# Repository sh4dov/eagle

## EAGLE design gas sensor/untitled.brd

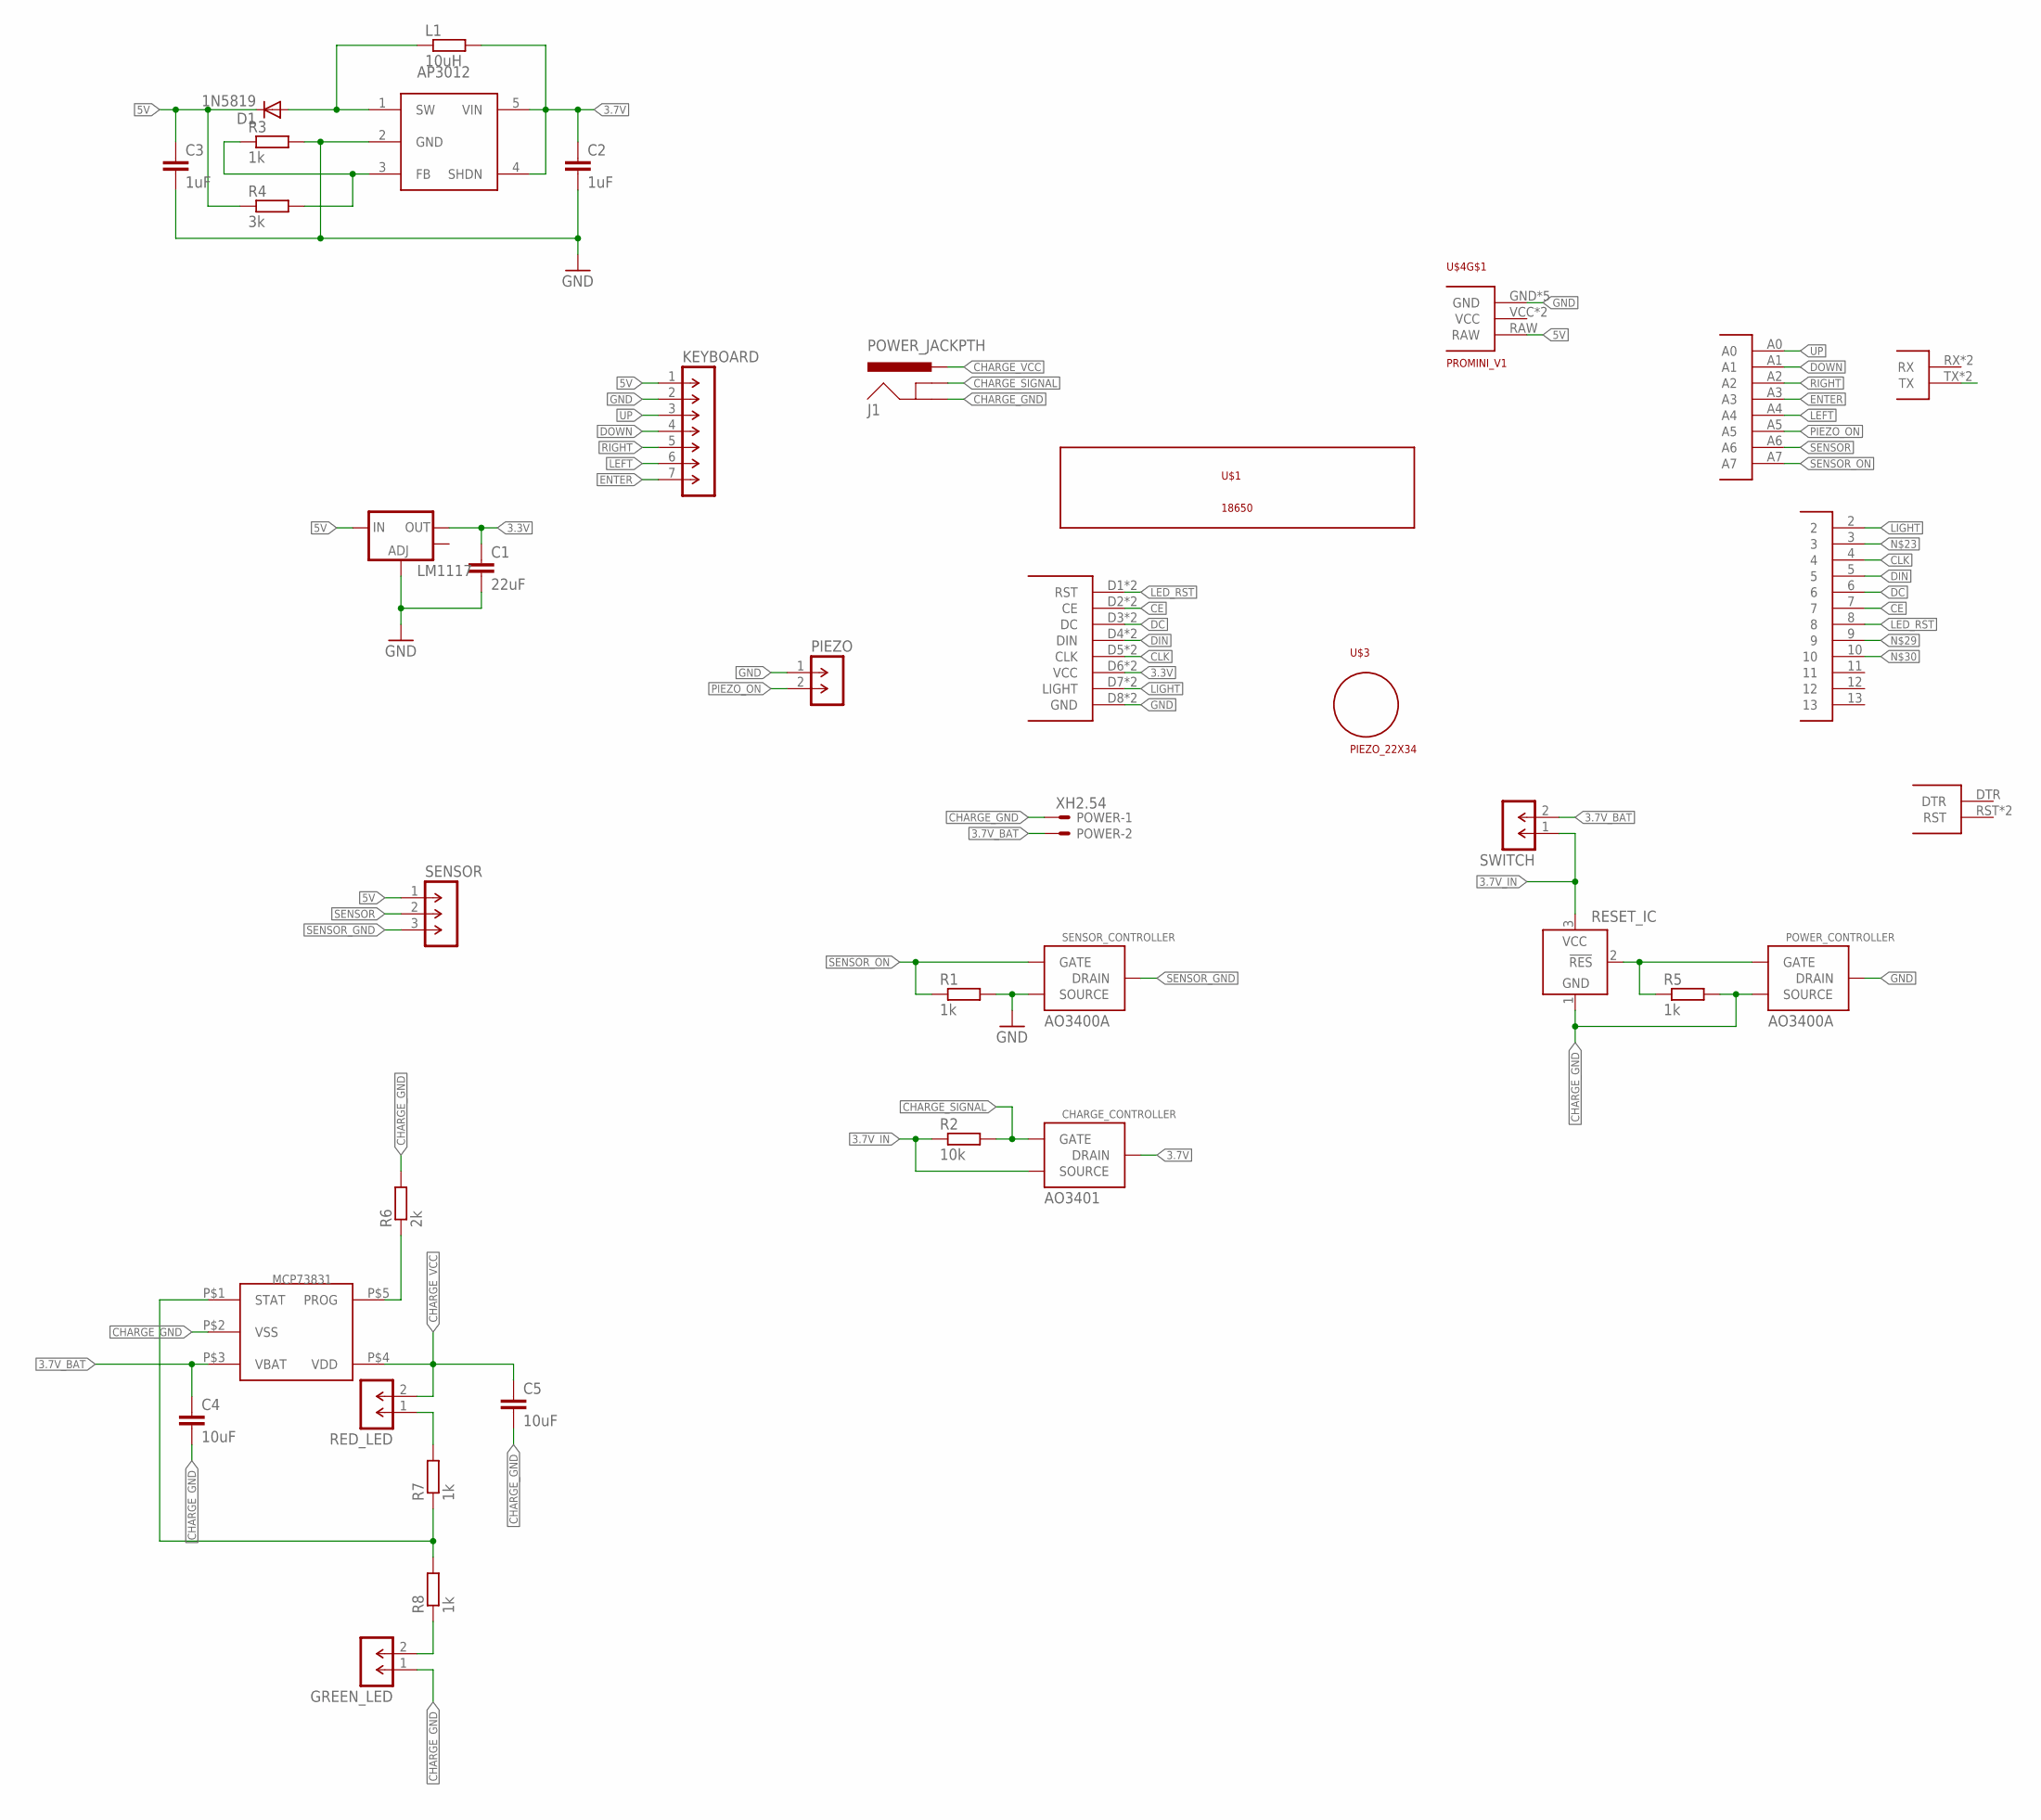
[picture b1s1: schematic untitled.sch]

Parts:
C1: 22uF; C0805K
C2, C3: 1uF; C1206
C4, C5: 10uF; C0805
CHARGE_CONTROLLER: AO3401; SOT-23
D1: 1N5819; DO214AC
GREEN_LED: M-1X02-SIP-100-32Y; SIP-100-02-32Y
J1: POWER_JACKPTH; POWER_JACK_PTH
KEYBOARD: M-1X07-SIP-100-32Y; SIP-100-07-32Y
L1: 10uH; R0805
LM1117: V_REG_LM1117SOT223; SOT223
MCP73831: MCP73831; 5PIN_SOT23
PIEZO: M-1X02-SIP-100-32Y; SIP-100-02-32Y
POWER: XH2.54
POWER_CONTROLLER: AO3400A; SOT-23
R1, R3, R5, R7, R8: 1k; R1206
R2: 10k; R1206
R4: 3k; R1206
R6: 2k; R1206
RED_LED: M-1X02-SIP-100-32Y; SIP-100-02-32Y
RESET_IC: TCM809; SOT23B-3
SENSOR: M-1X03-SIP-100-32Y; SIP-100-03-32Y
SENSOR_CONTROLLER: AO3400A; SOT-23
SWITCH: M-1X02-SIP-100-32Y; SIP-100-02-32Y
U$1: 18650
U$2: NOKIA_5110
U$3: PIEZO_22X34
U$4: PROMINI_V1
U$8: AP3012; SOT-23-5

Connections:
3.3V: C1.1, LM1117.2 (OUT), U$2.D6 (VCC), U$2.U6 (VCC)
3.7V: C2.1, CHARGE_CONTROLLER.3 (DRAIN), L1.2, U$8.4 (SHDN), U$8.5 (VIN)
3.7V_BAT: C4.1, MCP73831.P$3 (VBAT), POWER.2, SWITCH.2
3.7V_IN: CHARGE_CONTROLLER.2 (SOURCE), R2.1, RESET_IC.3 (VCC), SWITCH.1
5V: C3.1, D1.C, KEYBOARD.1, LM1117.3 (IN), R4.1, SENSOR.1, U$4.RAW
CE: U$2.D2 (CE), U$2.U2 (CE), U$4.7
CHARGE_GND: C4.2, C5.2, GREEN_LED.1, J1.GND, MCP73831.P$2 (VSS), POWER.1, POWER_CONTROLLER.2 (SOURCE), R5.2, R6.2, RESET_IC.1 (GND)
CHARGE_SIGNAL: CHARGE_CONTROLLER.1 (GATE), J1.GNDBREAK, R2.2
CHARGE_VCC: C5.1, J1.PWR, MCP73831.P$4 (VDD), RED_LED.2
CLK: U$2.D5 (CLK), U$2.U5 (CLK), U$4.4
DC: U$2.D3 (DC), U$2.U3 (DC), U$4.6
DIN: U$2.D4 (DIN), U$2.U4 (DIN), U$4.5
DOWN: KEYBOARD.4, U$4.A1
ENTER: KEYBOARD.7, U$4.A3
GND: C1.2, C2.2, C3.2, KEYBOARD.2, LM1117.1 (ADJ), PIEZO.1, POWER_CONTROLLER.3 (DRAIN), R1.2, R3.2, SENSOR_CONTROLLER.2 (SOURCE), U$2.D8 (GND), U$2.U8 (GND), U$4.GND, U$4.GND2 (GND), U$4.GND3 (GND), U$4.GND4 (GND), U$4.GND5 (GND), U$8.2 (GND)
LED_RST: U$2.D1 (RST), U$2.U1 (RST), U$4.8
LEFT: KEYBOARD.6, U$4.A4
LIGHT: U$2.D7 (LIGHT), U$2.U7 (LIGHT), U$4.2
unnamed: GREEN_LED.2, R8.1
unnamed: U$4.TX, U$4.TX2 (TX)
unnamed: D1.A, L1.1, U$8.1 (SW)
unnamed: MCP73831.P$5 (PROG), R6.1
unnamed: R3.1, R4.2, U$8.3 (FB)
unnamed: R7.2, RED_LED.1
unnamed: MCP73831.P$1 (STAT), R7.1, R8.2
PIEZO_ON: PIEZO.2, U$4.A5
RIGHT: KEYBOARD.5, U$4.A2
SENSOR: SENSOR.2, U$4.A6
SENSOR_GND: SENSOR.3, SENSOR_CONTROLLER.3 (DRAIN)
SENSOR_ON: R1.1, SENSOR_CONTROLLER.1 (GATE), U$4.A7
SENSOR_ON1: POWER_CONTROLLER.1 (GATE), R5.1, RESET_IC.2 (!RES)
UP: KEYBOARD.3, U$4.A0

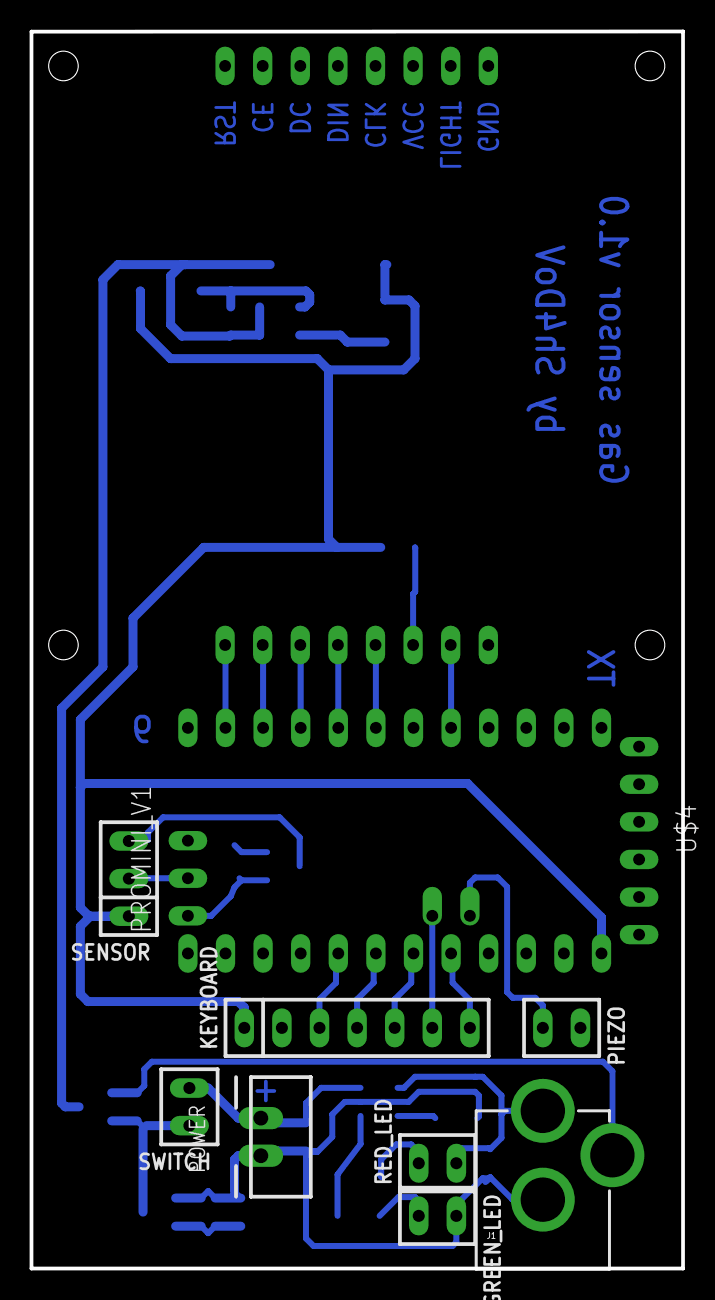
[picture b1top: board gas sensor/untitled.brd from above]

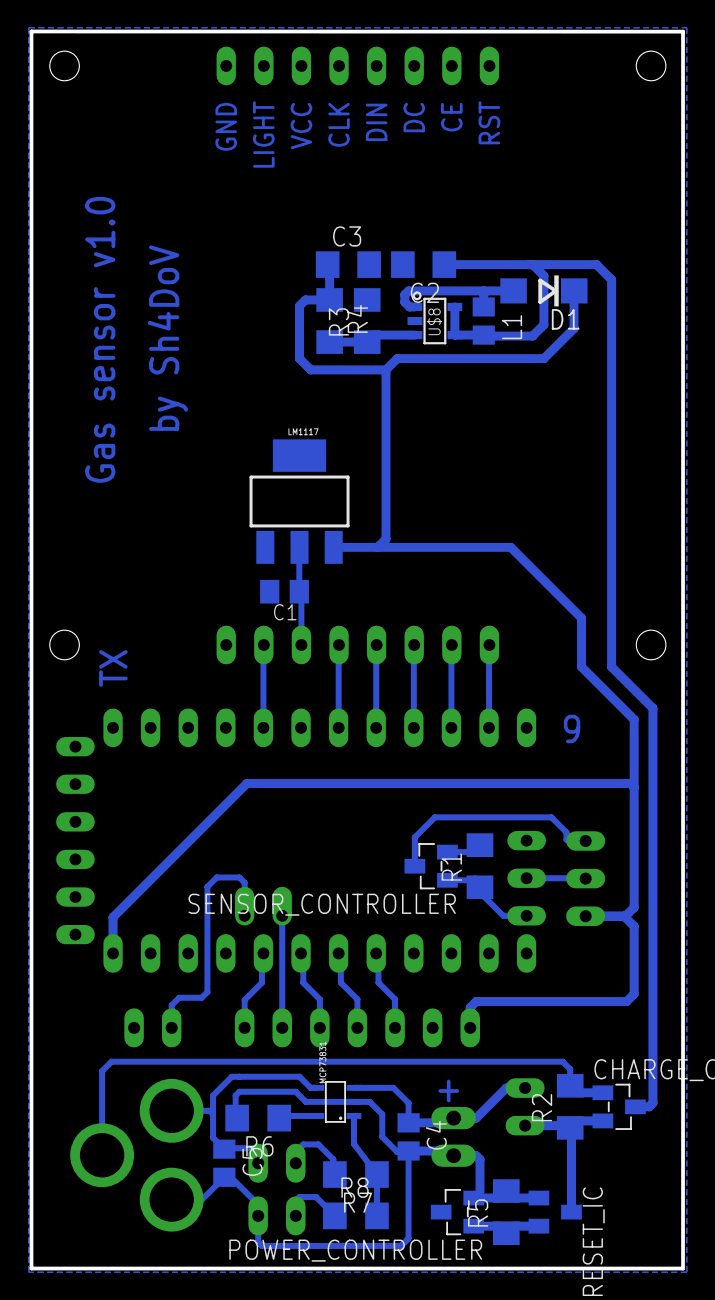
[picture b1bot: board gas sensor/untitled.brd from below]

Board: 2 copper layers, 44.0 x 83.6 mm, 34 parts (22 on the bottom side), 32 nets.

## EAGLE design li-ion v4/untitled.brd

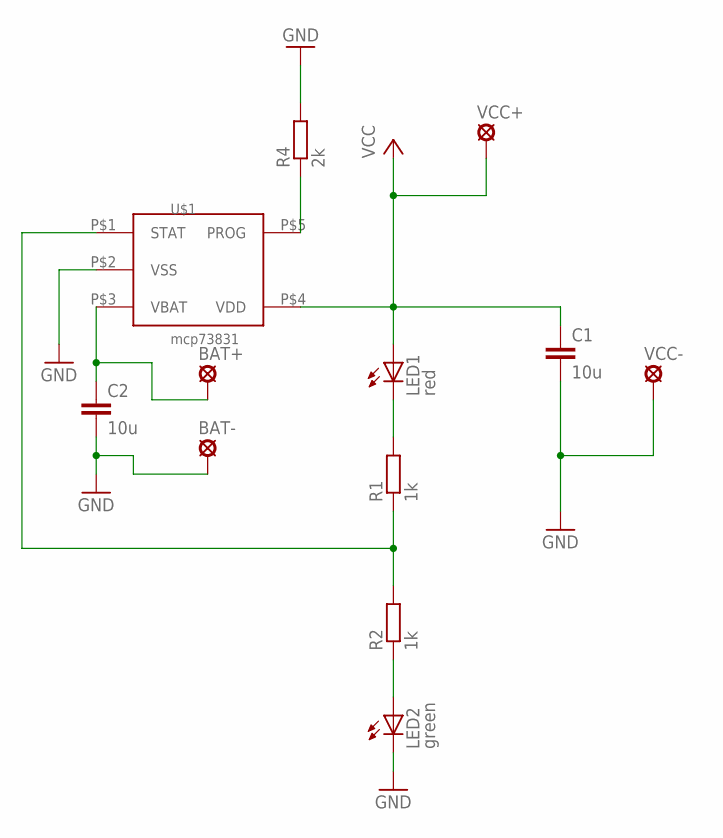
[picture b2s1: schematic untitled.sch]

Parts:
BAT+: LSP10
BAT-: LSP10
C1, C2: 10u; C0805
LED1: red; CHIPLED_0805
LED2: green; CHIPLED_0805
R1, R2: 1k; M1206
R4: 2k; M1206
U$1: mcp73831; 5PIN_SOT23
VCC+: LSP10
VCC-: LSP10

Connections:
GND: BAT-.MP, C1.2, C2.2, LED2.C, R4.2, U$1.P$2 (VSS), VCC-.MP
unnamed: R4.1, U$1.P$5 (PROG)
unnamed: LED1.C, R1.2
unnamed: R1.1, R2.2, U$1.P$1 (STAT)
unnamed: LED2.A, R2.1
unnamed: BAT+.MP, C2.1, U$1.P$3 (VBAT)
VCC: C1.1, LED1.A, U$1.P$4 (VDD), VCC+.MP

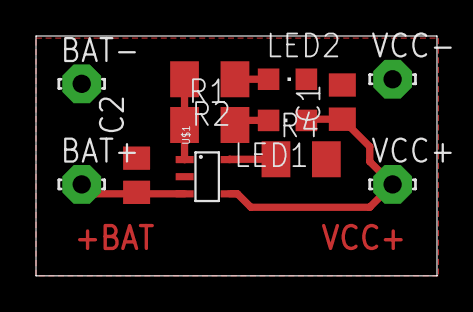
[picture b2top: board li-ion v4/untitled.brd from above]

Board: 2 copper layers, 22.3 x 13.3 mm, 12 parts (0 on the bottom side), 7 nets.

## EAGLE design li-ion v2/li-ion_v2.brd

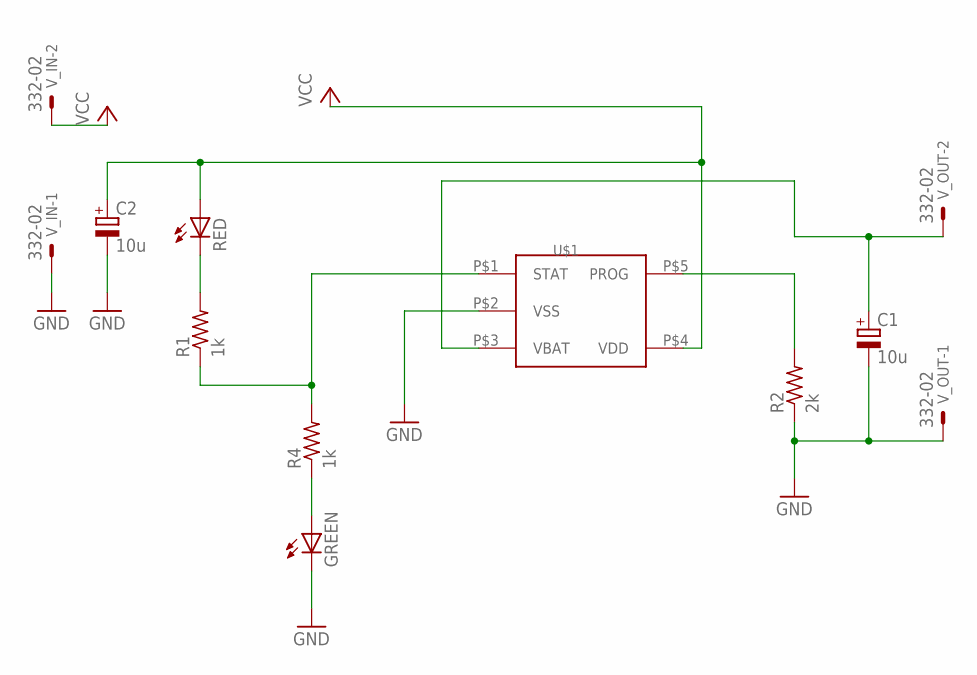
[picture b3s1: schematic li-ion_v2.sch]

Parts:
C1, C2: 10u; E1,8-4
GREEN: LED3MM
R1, R4: 1k; 0204/5
R2: 2k; 0204/5
RED: LED3MM
U$1: MCP73831; 5PIN_SOT23
V_IN: 332-02
V_OUT: 332-02

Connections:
GND: C1.-, C2.-, GREEN.K (C), R2.1, U$1.P$2 (VSS), V_IN.1, V_OUT.1
unnamed: C1.+, U$1.P$3 (VBAT), V_OUT.2
unnamed: R2.2, U$1.P$5 (PROG)
unnamed: R1.1, R4.2, U$1.P$1 (STAT)
unnamed: R1.2, RED.K (C)
unnamed: GREEN.A, R4.1
VCC: C2.+, RED.A, U$1.P$4 (VDD), V_IN.2

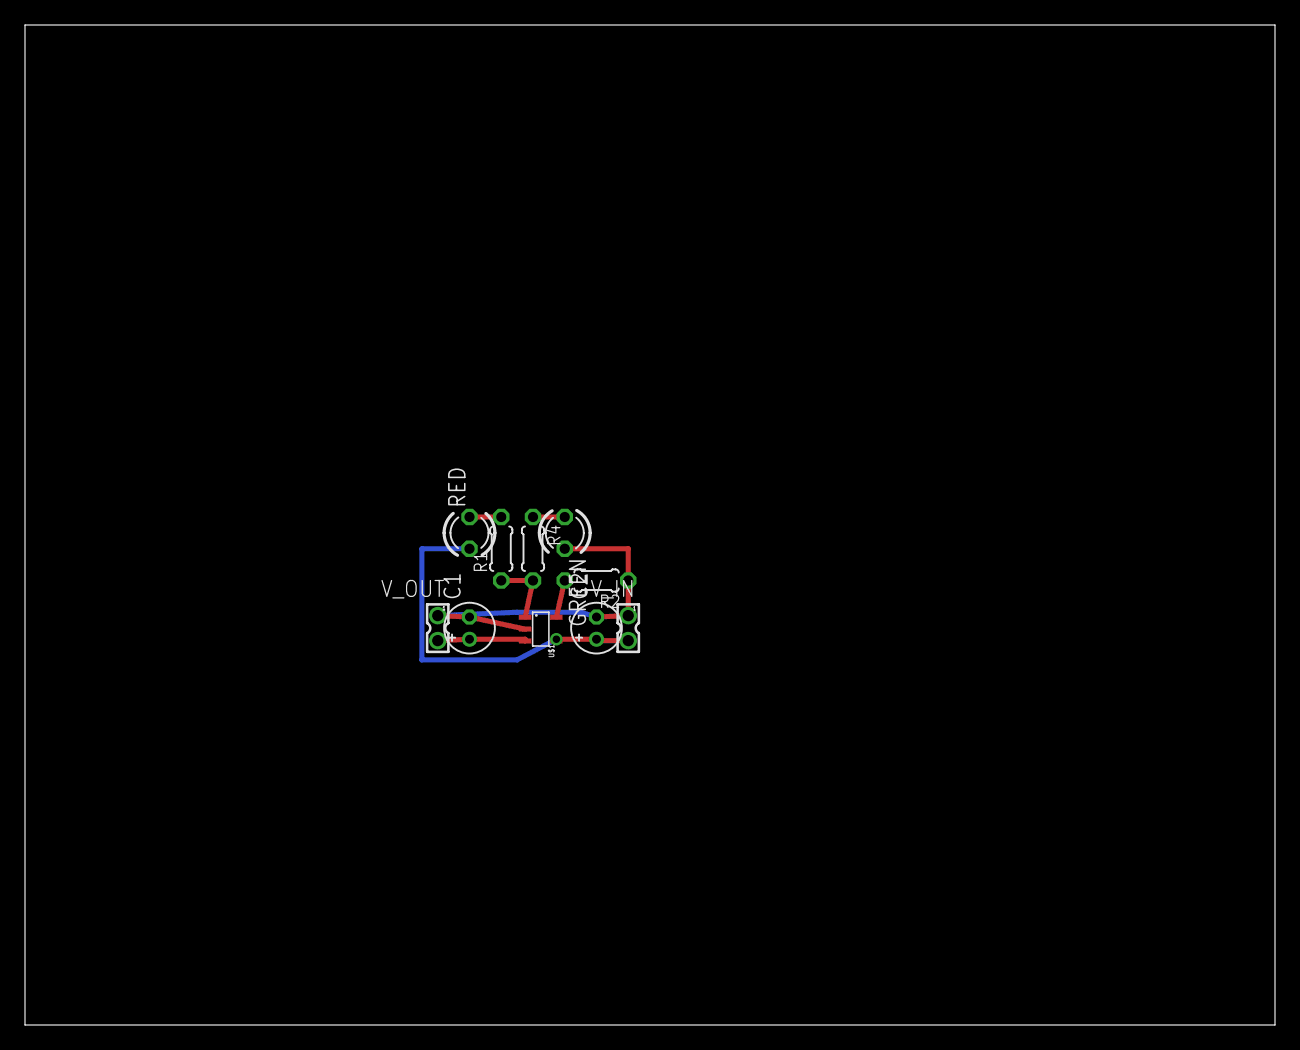
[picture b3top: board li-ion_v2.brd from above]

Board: 2 copper layers, 100.0 x 80.0 mm, 10 parts (0 on the bottom side), 7 nets.

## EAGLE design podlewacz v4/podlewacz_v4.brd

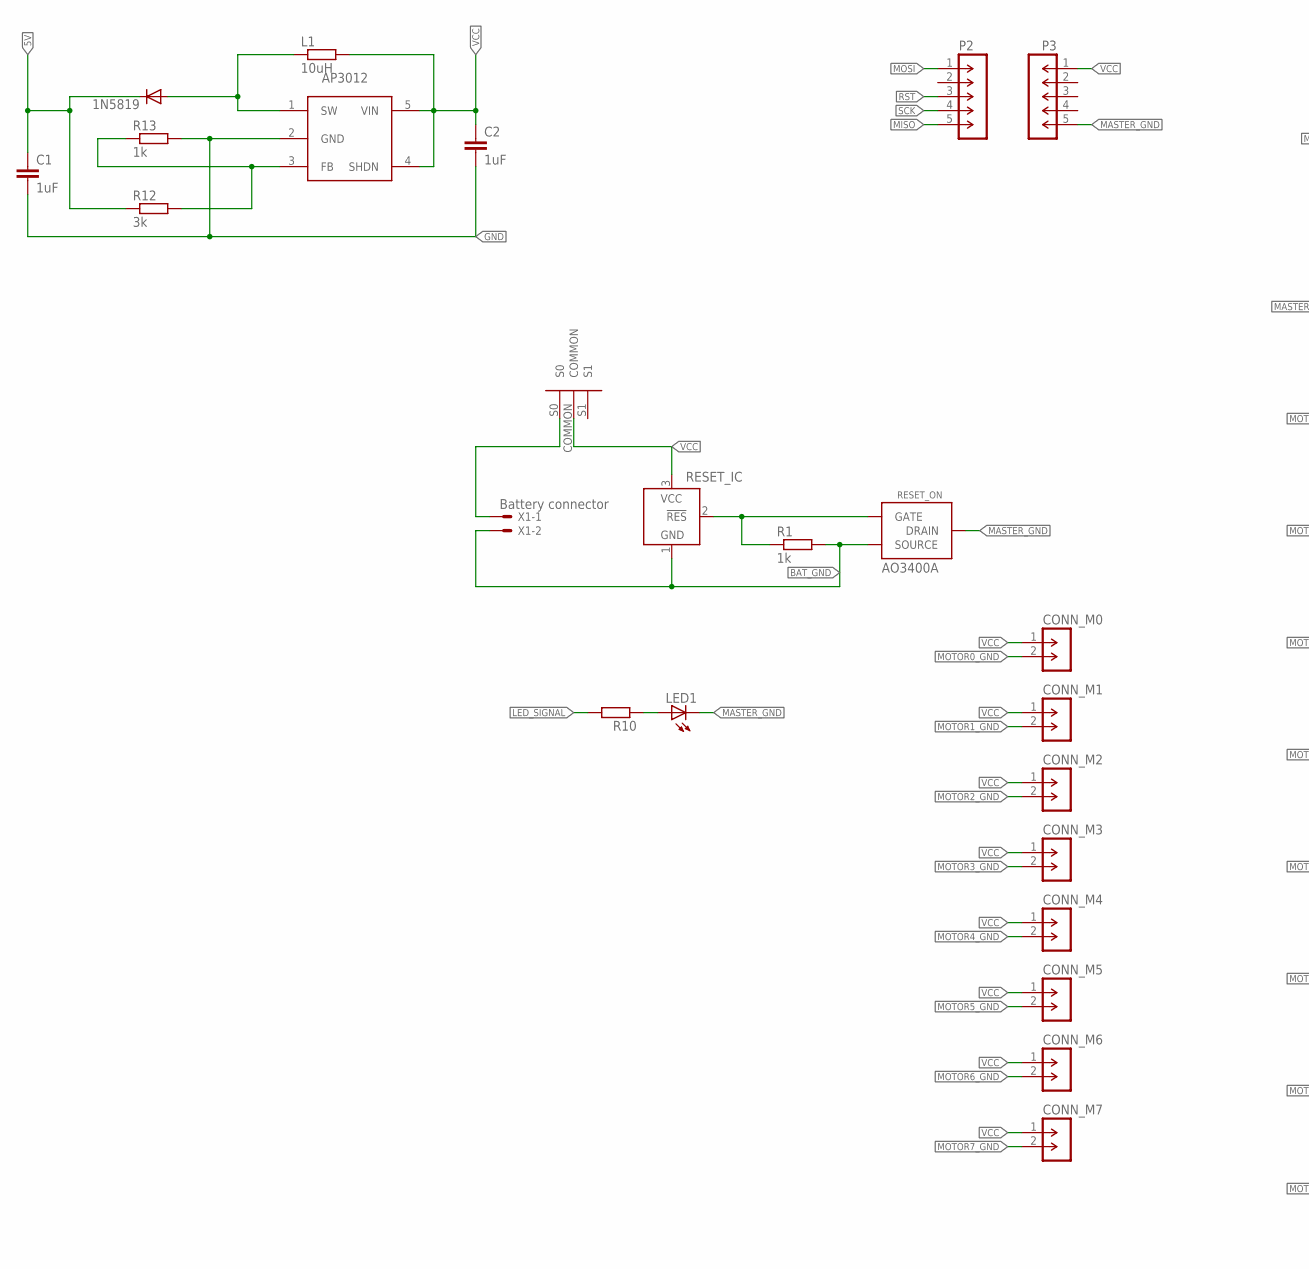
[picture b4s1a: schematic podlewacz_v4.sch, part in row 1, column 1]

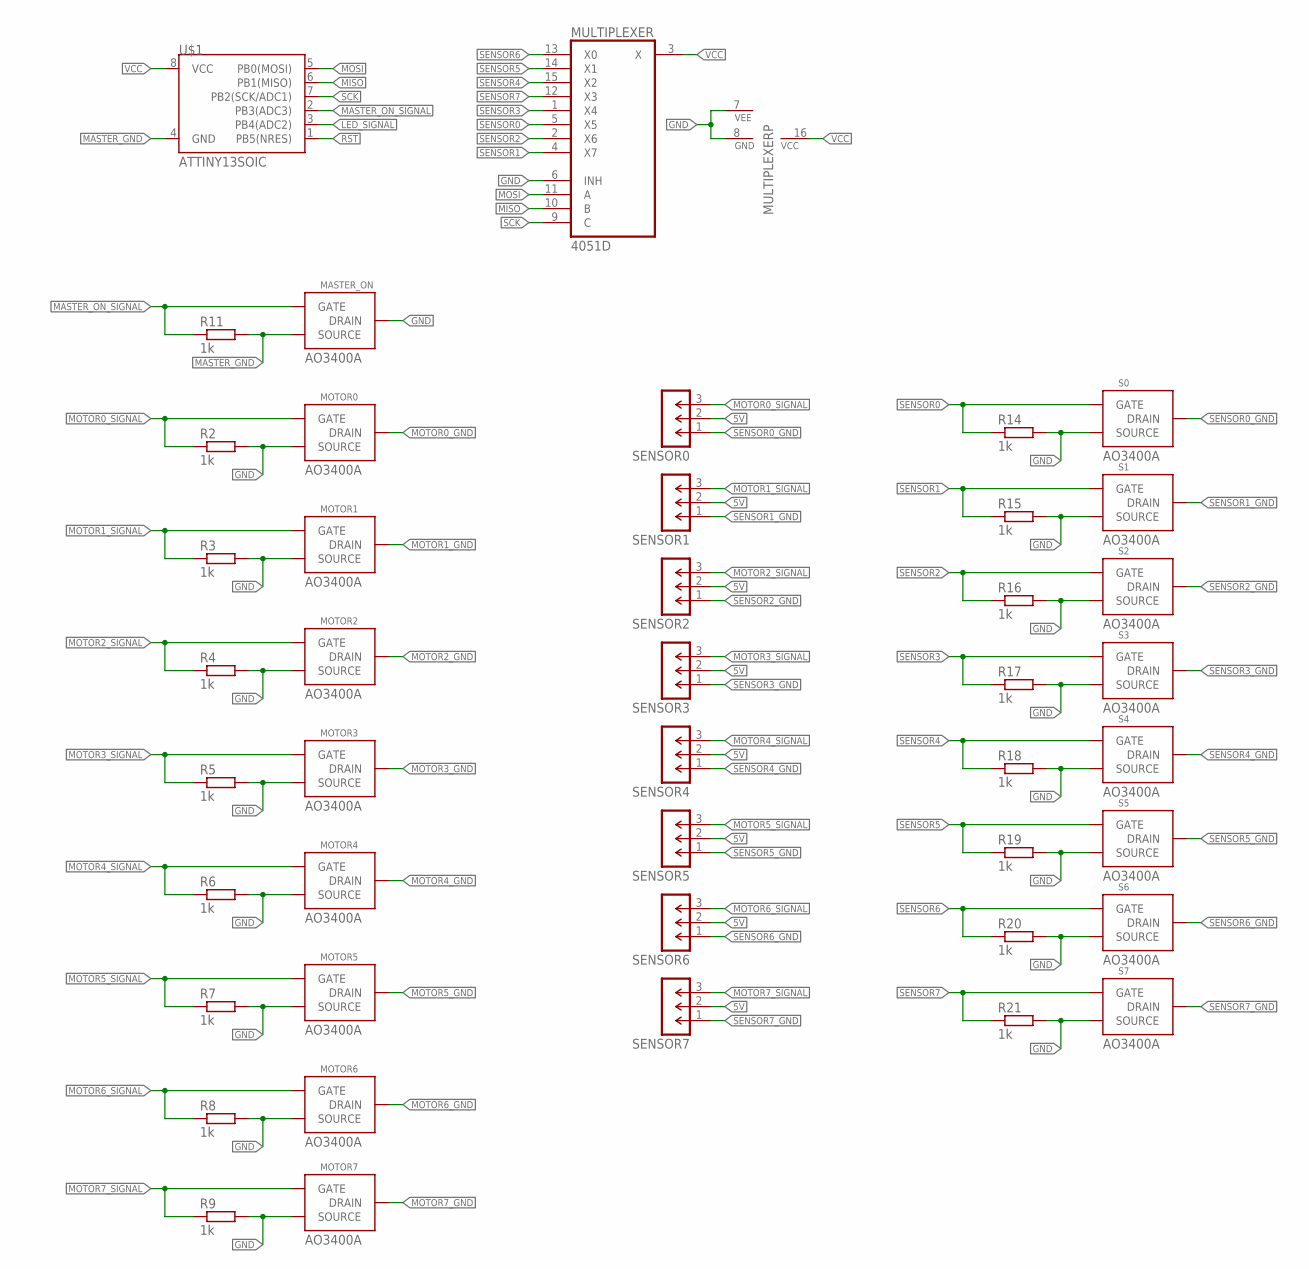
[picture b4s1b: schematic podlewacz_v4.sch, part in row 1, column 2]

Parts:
1N5819: DIODE-DO214AC; DO214AC
AP3012: AP3012; SOT-23-5
C1, C2: 1uF; C1206
CONN_M0, CONN_M1, CONN_M2, CONN_M3, CONN_M4, CONN_M5, CONN_M6, CONN_M7: M-1X02-SIP-100-32Y; SIP-100-02-32Y
L1: 10uH; R0805
LED1: LEDCHIP-LED0805; CHIP-LED0805
MASTER_ON: AO3400A; SOT-23
MOTOR0, MOTOR1, MOTOR2, MOTOR3, MOTOR4, MOTOR5, MOTOR6, MOTOR7: AO3400A; SOT-23
MULTIPLEXER: 4051D; SO16
P2, P3: M-1X05-SIP-100-32; SIP-100-05-32
R1, R2, R3, R4, R5, R6, R7, R8, R9, R11, R13, R14, R15, R16, R17, R18, R19, R20, R21: 1k; M1206
R10: R-EU_M0805; M0805
R12: 3k; M1206
RESET_IC: TCM809; SOT23B-3
RESET_ON: AO3400A; SOT-23
S0, S1, S2, S3, S4, S5, S6, S7: AO3400A; SOT-23
SENSOR0, SENSOR1, SENSOR2, SENSOR3, SENSOR4, SENSOR5, SENSOR6, SENSOR7: M-1X03-SIP-100-32Y; SIP-100-03-32Y
U$1: ATTINY13SOIC; SO08
U$2: SPDT_SLIDE_SWITCH_2_PITCH
X1: Battery connector; 22-23-2021

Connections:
5V: 1N5819.C, C1.1, R12.1, SENSOR0.2, SENSOR1.2, SENSOR2.2, SENSOR3.2, SENSOR4.2, SENSOR5.2, SENSOR6.2, SENSOR7.2
BAT_GND: R1.2, RESET_IC.1 (GND), RESET_ON.2 (SOURCE), X1.2
GND: AP3012.2 (GND), C1.2, C2.2, MASTER_ON.3 (DRAIN), MOTOR0.2 (SOURCE), MOTOR1.2 (SOURCE), MOTOR2.2 (SOURCE), MOTOR3.2 (SOURCE), MOTOR4.2 (SOURCE), MOTOR5.2 (SOURCE), MOTOR6.2 (SOURCE), MOTOR7.2 (SOURCE), MULTIPLEXER.6 (INH), MULTIPLEXER.7 (VEE), MULTIPLEXER.8 (GND), R2.2, R3.2, R4.2, R5.2, R6.2, R7.2, R8.2, R9.2, R13.2, R14.2, R15.2, R16.2, R17.2, R18.2, R19.2, R20.2, R21.2, S0.2 (SOURCE), S1.2 (SOURCE), S2.2 (SOURCE), S3.2 (SOURCE), S4.2 (SOURCE), S5.2 (SOURCE), S6.2 (SOURCE), S7.2 (SOURCE)
LED_SIGNAL: R10.2, U$1.3 (PB4(ADC2))
MASTER_GND: LED1.C, MASTER_ON.2 (SOURCE), P3.5, R11.2, RESET_ON.3 (DRAIN), U$1.4 (GND)
MASTER_ON: R1.1, RESET_IC.2 (!RES), RESET_ON.1 (GATE)
MASTER_ON_SIGNAL: MASTER_ON.1 (GATE), R11.1, U$1.2 (PB3(ADC3))
MISO: MULTIPLEXER.10 (B), P2.5, U$1.6 (PB1(MISO))
MOSI: MULTIPLEXER.11 (A), P2.1, U$1.5 (PB0(MOSI))
MOTOR0_GND: CONN_M0.2, MOTOR0.3 (DRAIN)
MOTOR0_SIGNAL: MOTOR0.1 (GATE), R2.1, SENSOR0.3
MOTOR1_GND: CONN_M1.2, MOTOR1.3 (DRAIN)
MOTOR1_SIGNAL: MOTOR1.1 (GATE), R3.1, SENSOR1.3
MOTOR2_GND: CONN_M2.2, MOTOR2.3 (DRAIN)
MOTOR2_SIGNAL: MOTOR2.1 (GATE), R4.1, SENSOR2.3
MOTOR3_GND: CONN_M3.2, MOTOR3.3 (DRAIN)
MOTOR3_SIGNAL: MOTOR3.1 (GATE), R5.1, SENSOR3.3
MOTOR4_GND: CONN_M4.2, MOTOR4.3 (DRAIN)
MOTOR4_SIGNAL: MOTOR4.1 (GATE), R6.1, SENSOR4.3
MOTOR5_GND: CONN_M5.2, MOTOR5.3 (DRAIN)
MOTOR5_SIGNAL: MOTOR5.1 (GATE), R7.1, SENSOR5.3
MOTOR6_GND: CONN_M6.2, MOTOR6.3 (DRAIN)
MOTOR6_SIGNAL: MOTOR6.1 (GATE), R8.1, SENSOR6.3
MOTOR7_GND: CONN_M7.2, MOTOR7.3 (DRAIN)
MOTOR7_SIGNAL: MOTOR7.1 (GATE), R9.1, SENSOR7.3
unnamed: U$2.S0, X1.1
unnamed: LED1.A, R10.1
unnamed: 1N5819.A, AP3012.1 (SW), L1.1
unnamed: AP3012.3 (FB), R12.2, R13.1
RST: P2.3, U$1.1 (PB5(NRES))
SCK: MULTIPLEXER.9 (C), P2.4, U$1.7 (PB2(SCK/ADC1))
SENSOR0: MULTIPLEXER.5 (X5), R14.1, S0.1 (GATE)
SENSOR0_GND: S0.3 (DRAIN), SENSOR0.1
SENSOR1: MULTIPLEXER.4 (X7), R15.1, S1.1 (GATE)
SENSOR1_GND: S1.3 (DRAIN), SENSOR1.1
SENSOR2: MULTIPLEXER.2 (X6), R16.1, S2.1 (GATE)
SENSOR2_GND: S2.3 (DRAIN), SENSOR2.1
SENSOR3: MULTIPLEXER.1 (X4), R17.1, S3.1 (GATE)
SENSOR3_GND: S3.3 (DRAIN), SENSOR3.1
SENSOR4: MULTIPLEXER.15 (X2), R18.1, S4.1 (GATE)
SENSOR4_GND: S4.3 (DRAIN), SENSOR4.1
SENSOR5: MULTIPLEXER.14 (X1), R19.1, S5.1 (GATE)
SENSOR5_GND: S5.3 (DRAIN), SENSOR5.1
SENSOR6: MULTIPLEXER.13 (X0), R20.1, S6.1 (GATE)
SENSOR6_GND: S6.3 (DRAIN), SENSOR6.1
SENSOR7: MULTIPLEXER.12 (X3), R21.1, S7.1 (GATE)
SENSOR7_GND: S7.3 (DRAIN), SENSOR7.1
VCC: AP3012.4 (SHDN), AP3012.5 (VIN), C2.1, CONN_M0.1, CONN_M1.1, CONN_M2.1, CONN_M3.1, CONN_M4.1, CONN_M5.1, CONN_M6.1, CONN_M7.1, L1.2, MULTIPLEXER.3 (X), MULTIPLEXER.16 (VCC), P3.1, RESET_IC.3 (VCC), U$1.8 (VCC), U$2.COMMON

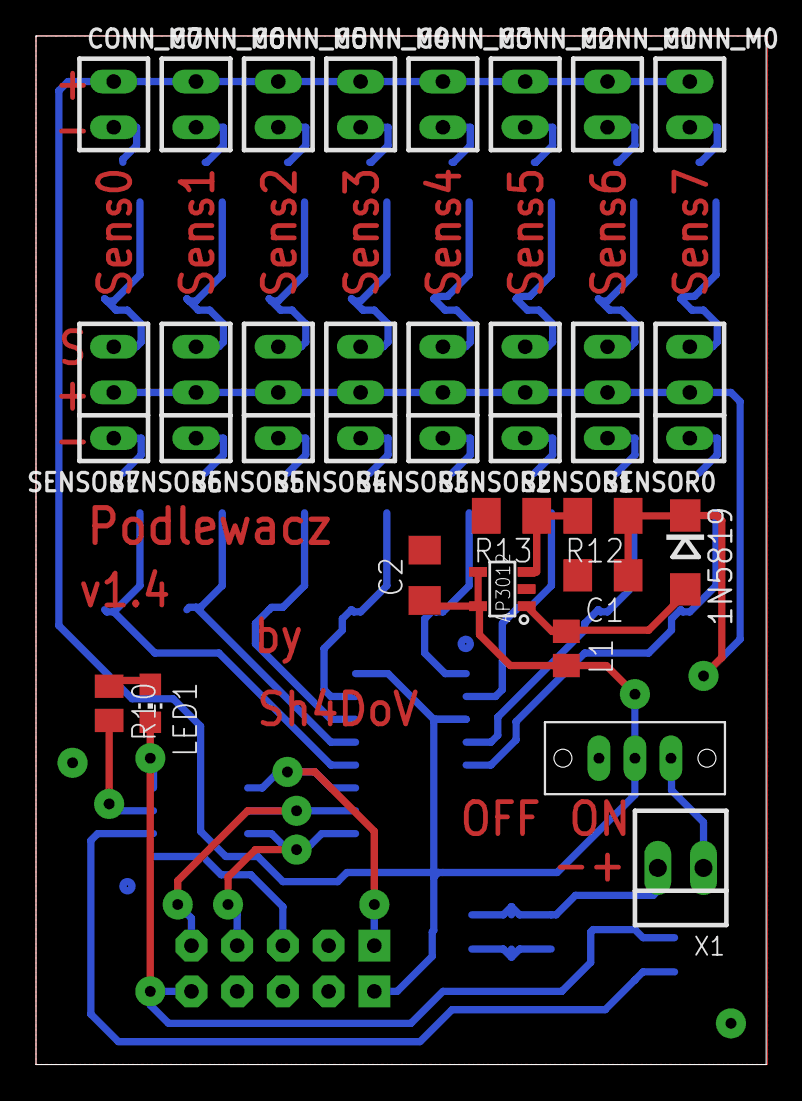
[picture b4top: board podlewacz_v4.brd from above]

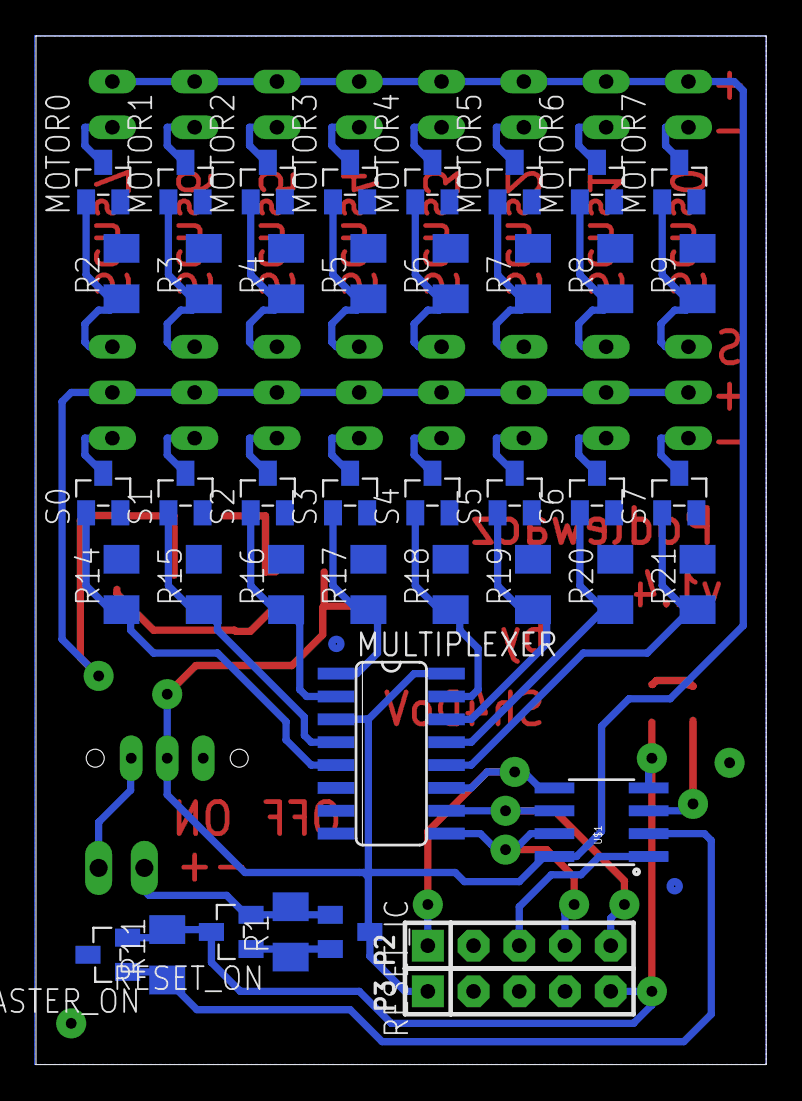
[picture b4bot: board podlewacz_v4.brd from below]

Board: 2 copper layers, 40.6 x 57.1 mm, 68 parts (41 on the bottom side), 48 nets.

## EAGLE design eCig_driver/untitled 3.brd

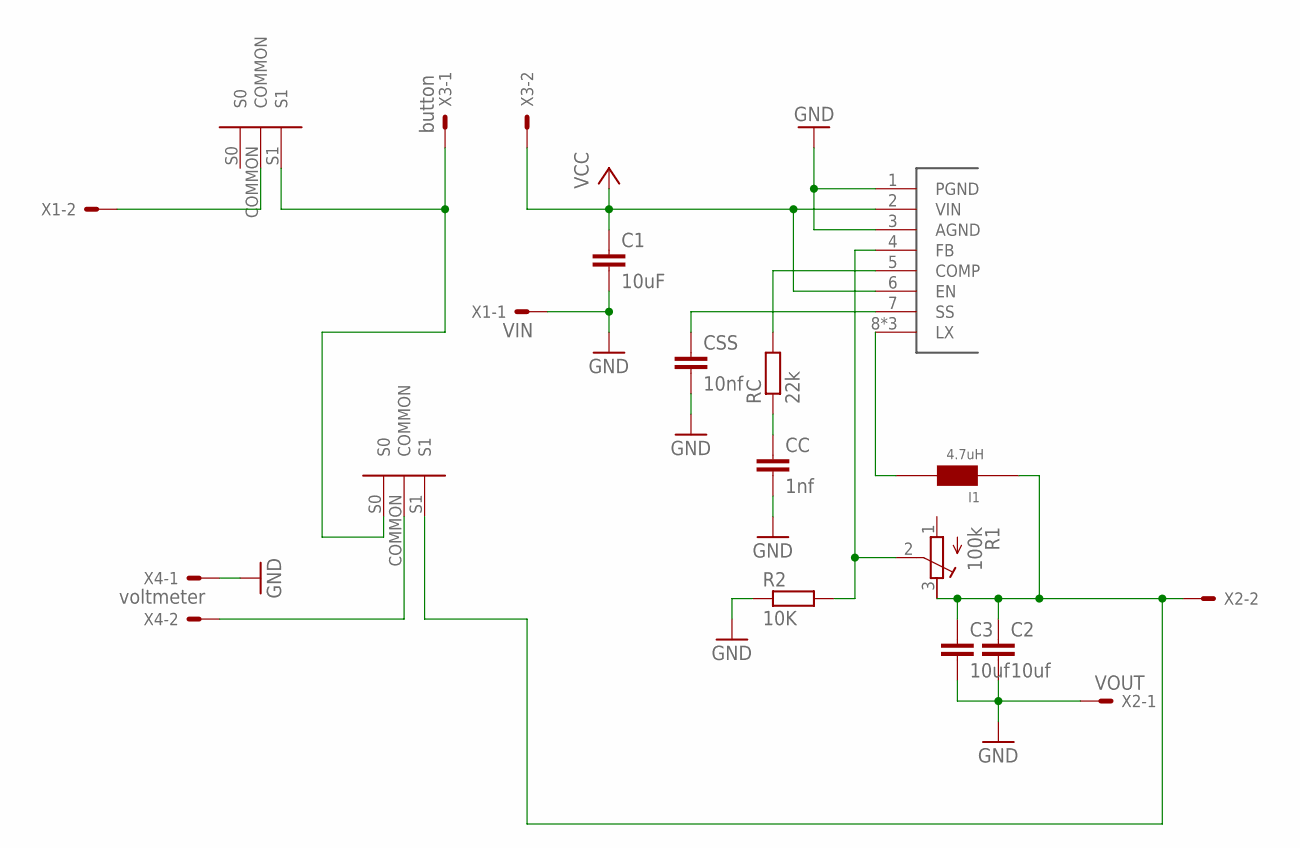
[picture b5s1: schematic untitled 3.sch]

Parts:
C1: 10uF; C0805K
C2, C3: 10uf; C0805K
CC: 1nf; C1206K
CSS: 10nf; C1206K
I1: 4.7uH; RH127
MASTER_ON: SPDT_SLIDE_SWITCH_2_PITCH
METER_SWITCH: SPDT_SLIDE_SWITCH_2_PITCH
R1: 100k; RTRIM64W
R2: 10K; R1206
RC: 22k; R1206
U$3: AOZ1051PI
X1: VIN; XH2.54
X2: VOUT; XH2.54
X3: button; XH2.54
X4: voltmeter; XH2.54

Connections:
GND: C1.2, C2.2, C3.2, CC.2, CSS.2, R2.1, U$3.1 (PGND), U$3.3 (AGND), X1.1, X2.1, X4.1
unnamed: RC.2, U$3.5 (COMP)
unnamed: CC.1, RC.1
unnamed: R1.2 (S), R2.2, U$3.4 (FB)
unnamed: CSS.1, U$3.7 (SS)
unnamed: METER_SWITCH.COMMON, X4.2
unnamed: I1.P$1, U$3.8 (LX), U$3.P$1 (LX), U$3.P$2 (LX)
unnamed: C2.1, C3.1, I1.P$2, METER_SWITCH.S1, R1.3 (E), X2.2
unnamed: MASTER_ON.COMMON, X1.2
unnamed: MASTER_ON.S1, METER_SWITCH.S0, X3.1
VCC: C1.1, U$3.2 (VIN), U$3.6 (EN), X3.2

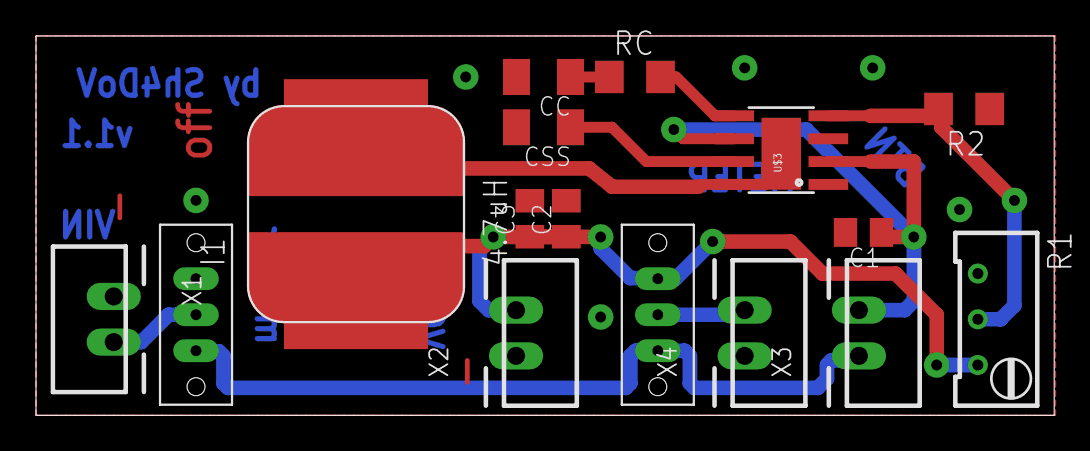
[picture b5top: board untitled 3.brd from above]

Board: 2 copper layers, 56.6 x 21.1 mm, 16 parts (0 on the bottom side), 11 nets.

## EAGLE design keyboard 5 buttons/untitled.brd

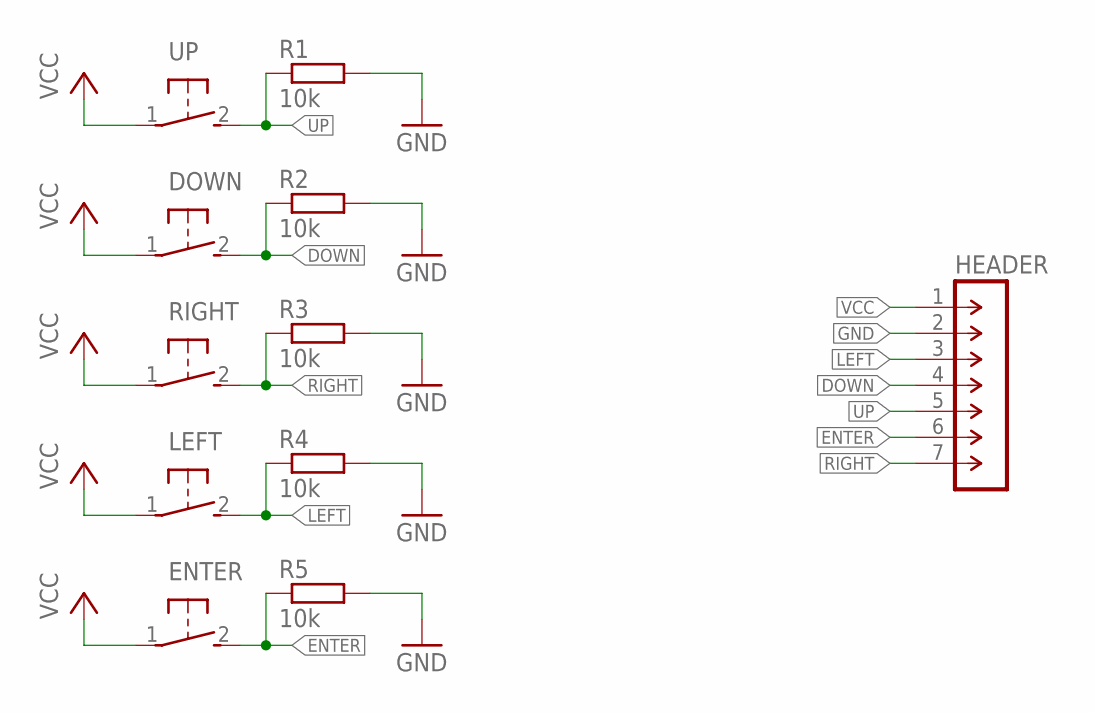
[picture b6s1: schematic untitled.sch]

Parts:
DOWN: DTSM-3
ENTER: DTSM-3
HEADER: M-1X07-SIP-100-32Y; SIP-100-07-32Y
LEFT: DTSM-3
R1, R2, R3, R4, R5: 10k; R1206
RIGHT: DTSM-3
UP: DTSM-3

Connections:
DOWN: DOWN.2, HEADER.4, R2.1
ENTER: ENTER.2, HEADER.6, R5.1
GND: HEADER.2, R1.2, R2.2, R3.2, R4.2, R5.2
LEFT: HEADER.3, LEFT.2, R4.1
RIGHT: HEADER.7, R3.1, RIGHT.2
UP: HEADER.5, R1.1, UP.2
VCC: DOWN.1, ENTER.1, HEADER.1, LEFT.1, RIGHT.1, UP.1

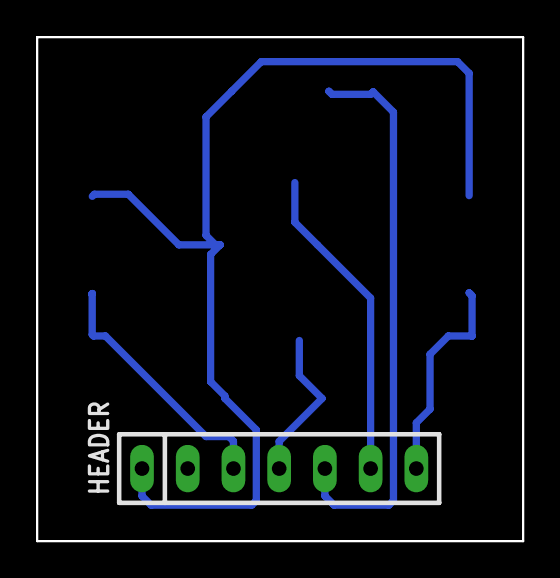
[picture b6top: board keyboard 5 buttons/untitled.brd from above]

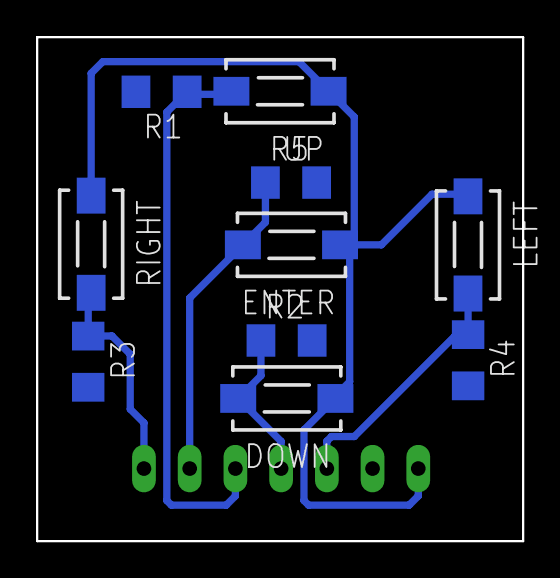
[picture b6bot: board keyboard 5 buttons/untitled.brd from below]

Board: 2 copper layers, 27.0 x 28.0 mm, 11 parts (10 on the bottom side), 7 nets.

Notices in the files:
parts and their libraries:
con-headers-jp: Copyright (C) 2008, Bob Starr
SparkFun-PowerIC: Licensing: Creative Commons ShareAlike 4.0 International - https://creativecommons.org/licenses/by-sa/4.0
